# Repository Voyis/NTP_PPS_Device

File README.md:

# NTP_PPP_Device
ESP32 based board that mimics an GPS with PPS, but using NTP.

## Software Install

This project uses the Arduino library to build the code and flash it onto the ESP32-WROOM-32 from Espressif. After installing the Arduino IDE, you have to first instal the Adafruit SSD1360 library and all it's dependencies. You also need to install the [ESP32 board package](https://docs.espressif.com/projects/arduino-esp32/en/latest/installing.html#installing-using-boards-manager).

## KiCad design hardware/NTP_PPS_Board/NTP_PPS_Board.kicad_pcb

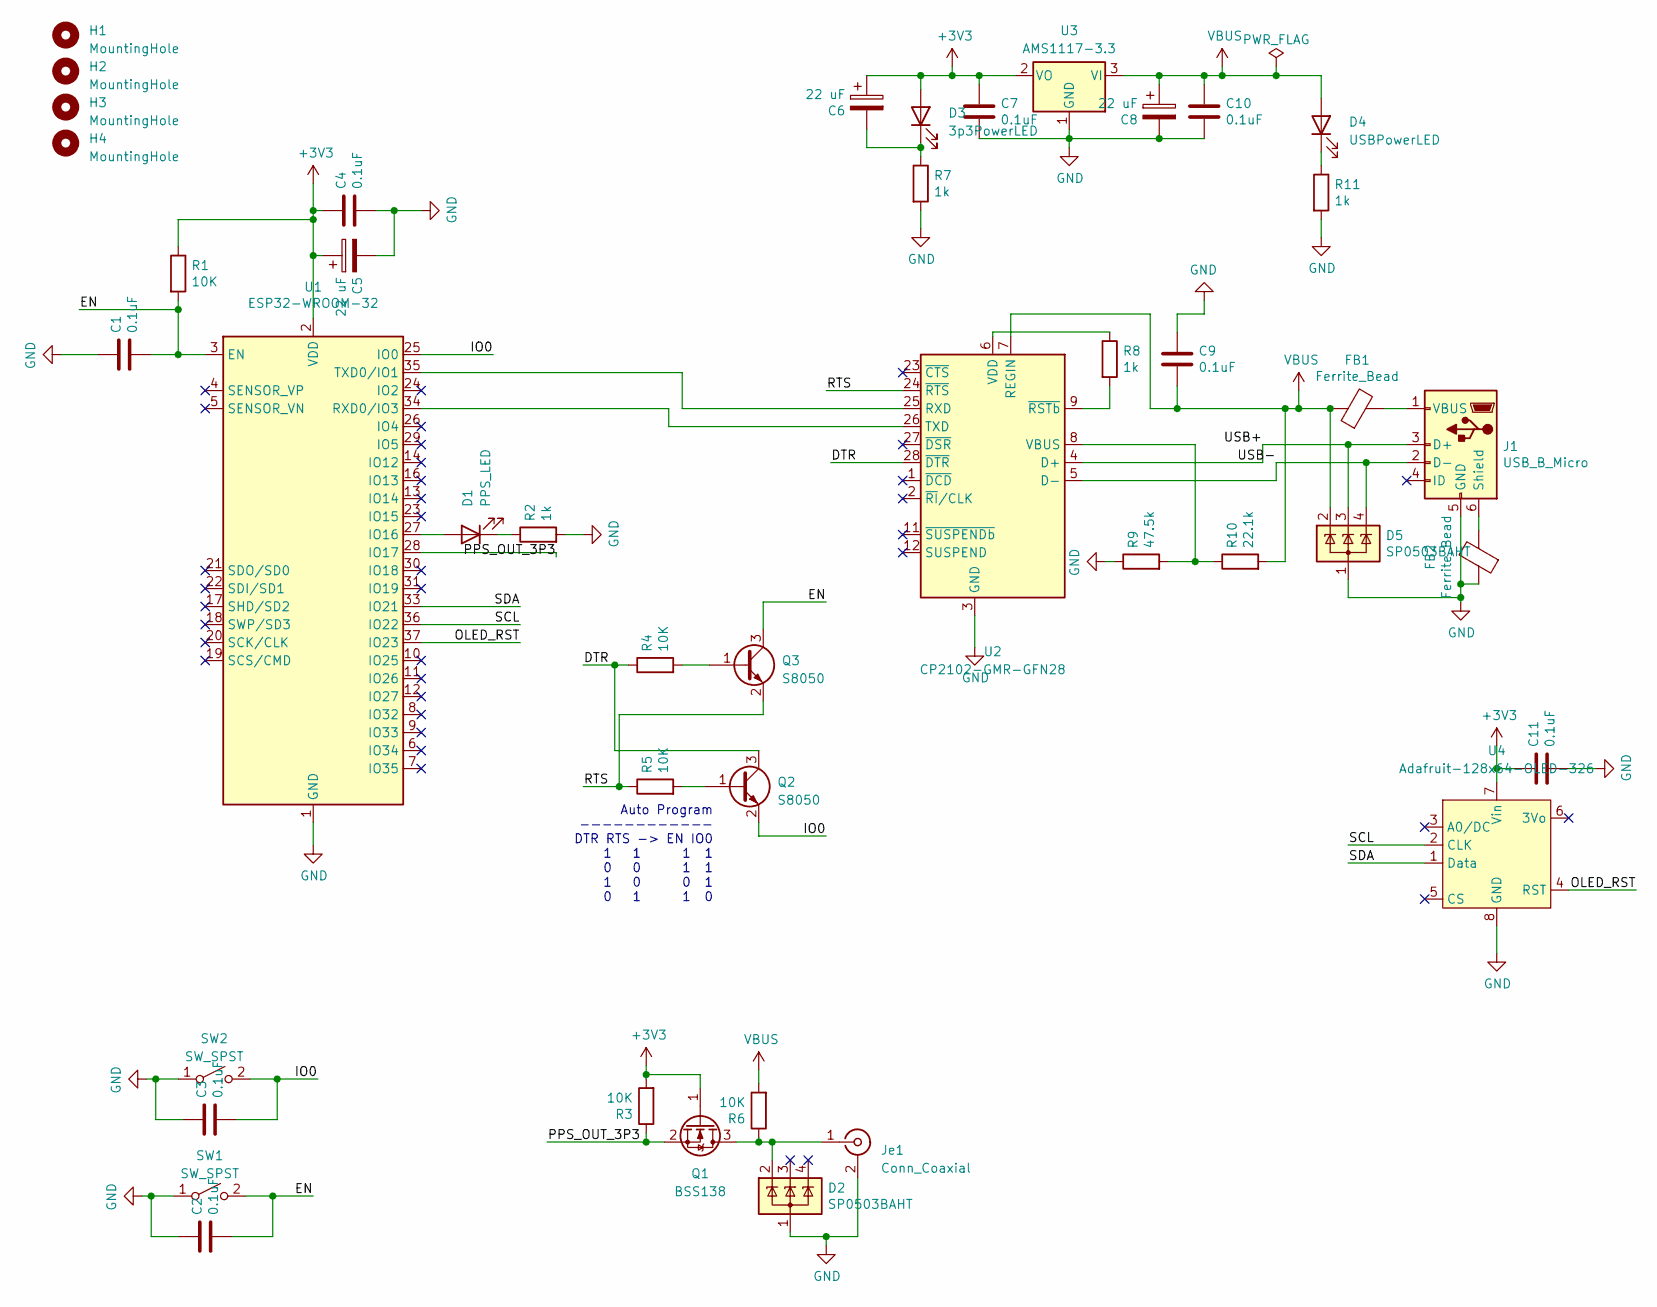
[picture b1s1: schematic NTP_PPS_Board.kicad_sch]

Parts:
C1, C2, C3, C4, C7, C9, C10, C11: 0.1uF; C_0603_1608Metric; LCSC Part # C14663
C5, C6, C8: 22 uF; CP_Elec_6.3x5.4; LCSC Part # C27783
D1: PPS_LED; LED_0603_1608Metric; LCSC Part # C74343
D2, D5: SP0503BAHT; SOT-143; LCSC Part # C7074
D3: 3p3PowerLED; LED_0603_1608Metric; LCSC Part # C72044
D4: USBPowerLED; LED_0603_1608Metric; LCSC Part # C72044
FB1, FB2: Ferrite_Bead; L_0805_2012Metric; LCSC Part # C88993
H1, H2, H3, H4: MountingHole; MountingHole_3.2mm_M3
J1: USB_B_Micro; MicroUSB-5.9mm; LCSC Part # C393940
Je1: Conn_Coaxial; BNC_TEConnectivity_1478204_Vertical; Digikey Part # A97581-ND
Q1: BSS138; SOT-23; LCSC Part # C112239
Q2, Q3: S8050; SOT-23; LCSC Part # C727137
R1, R3, R4, R5, R6: 10K; R_0603_1608Metric; LCSC Part # C269701
R2, R7, R8, R11: 1k; C_0603_1608Metric; LCSC Part # C269349
R9: 47.5k; R_0603_1608Metric; LCSC Part # C325696
R10: 22.1k; R_0603_1608Metric; LCSC Part # C269476
SW1, SW2: SW_SPST; SW_Push_1P1T_NO_6x6mm_H9.5mm; LCSC Part # C2686880
U1: ESP32-WROOM-32; Digikey Part # 1965-ESP32-WROOM-32E(4MBHIGHTEMP)CT-ND
U2: CP2102-GMR-GFN28; QFN-28-1EP_5x5mm_P0.5mm_EP3.35x3.35mm; LCSC Part # C6568
U3: AMS1117-3.3; SOT-223-3_TabPin2; LCSC Part # C351784
U4: Adafruit-128x64-OLED-326; AdaFruit-0.86-OLED

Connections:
+3V3: C4.1, C5.1, C6.1, C7.1, C11.1, D3.2 (A), Q1.1 (G), R1.1, R3.2, U1.2 (VDD), U3.2 (VO), U4.7 (Vin)
/DTR: Q2.3 (C), R4.1, U2.28 (~DTR)
/EN: C1.2, C2.2, Q3.3 (C), R1.2, SW1.2 (B), U1.3 (EN)
/IO0: C3.2, Q2.2 (E), SW2.2 (B), U1.25 (IO0)
/OLED_RST: U1.37 (IO23), U4.4 (RST)
/PPS_OUT_3P3: Q1.2 (S), R3.1, U1.28 (IO17)
/RTS: Q3.2 (E), R5.1, U2.24 (~RTS)
/SCL: U1.36 (IO22), U4.2 (CLK)
/SDA: U1.33 (IO21), U4.1 (Data)
/USB+: D5.3 (K), J1.3 (D+), U2.4 (D+)
/USB-: D5.4 (K), J1.2 (D-), U2.5 (D-)
GND: C1.1, C2.1, C3.1, C4.2, C5.2, C7.2, C8.2, C9.1, C10.2, C11.2, D2.1 (A), D5.1 (A), FB2.1, J1.5 (GND), Je1.2 (Ext), R2.2, R7.2, R9.1, R11.2, SW1.1 (A), SW2.1 (A), U1.1 (GND), U1.15 (GND), U1.38 (GND), U1.39 (GND), U2.3 (GND), U2.29 (GND), U3.1 (GND), U4.8 (GND)
unnamed: C6.2, D3.1 (K), R7.1
unnamed: D1.1 (K), R2.1
unnamed: D1.2 (A), U1.27 (IO16)
unnamed: D2.2 (K), Je1.1 (In), Q1.3 (D), R6.1
unnamed: D4.1 (K), R11.1
unnamed: FB1.2, J1.1 (VBUS)
unnamed: FB2.2, J1.6 (Shield)
unnamed: Q2.1 (B), R5.2
unnamed: Q3.1 (B), R4.2
unnamed: R8.1, U2.6 (VDD)
unnamed: R8.2, U2.9 (~RSTb)
unnamed: R9.2, R10.1, U2.8 (VBUS)
unnamed: U1.34 (RXD0/IO3), U2.26 (TXD)
unnamed: U1.35 (TXD0/IO1), U2.25 (RXD)
VBUS: C8.1, C9.2, C10.1, D4.2 (A), D5.2 (K), FB1.1, R6.2, R10.2, U2.7 (REGIN), U3.3 (VI)

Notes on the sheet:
Auto Program ------------ DTR RTS -> EN IO0 1 1 1 1 0 0 1 1 1 0 0 1 0 1 1 0

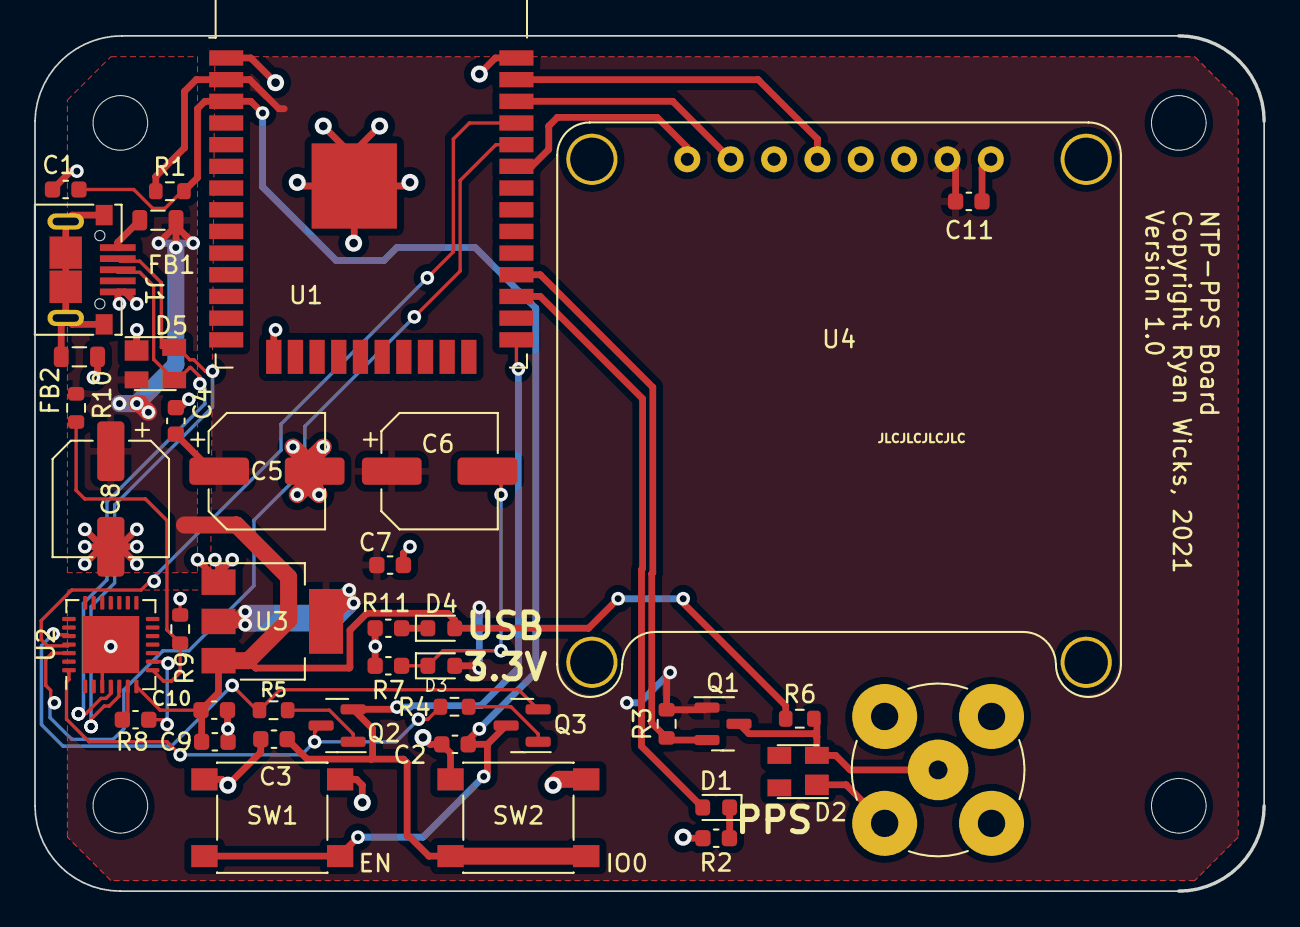
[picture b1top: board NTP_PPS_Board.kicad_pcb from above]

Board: 2 copper layers, 72.0 x 50.1 mm, 44 parts (0 on the bottom side), 27 nets.

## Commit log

2021-04-21 First commit.
2021-04-22 Work on the boards continues.
2021-04-23 Finished schematic.
2021-04-23 Added circuit board
2021-04-25 Board design finished.
2021-04-26 Added all the manufacturing files and updated position and BOM files (needed some modifications).
2021-05-10 Added software for PPS generator.
2021-05-12 Time working, Wifi working, display working. Still needs serial and socket ZDA out.
2021-05-13 Added support for ZDA reading over serial, TCP and UDP.
2021-05-13 Serial and TCP working. UDP untested.
2021-10-29 update zda out
2022-08-10 Added headless NTP nano generator arduino code.
2022-08-20 Add cmds
2022-08-23 Fix testing mistake
2024-03-08 Update NTP_PPS_Generator.ino
    Update to V2 board. Change pin assignments for LED and output
2025-02-24 RMC Messages added to GPS message

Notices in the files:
hardware/NTP_PPS_Board/NTP_PPS_Board.kicad_pcb:
Copyright Ryan Wicks, 2021
